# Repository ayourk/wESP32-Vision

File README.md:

# wESP32-Vision
OV2640 Camera module AddOn board for wESP32

## Description
This is my reinterpretation of [@xorbit](https://github.com/xorbit)'s Camera module prototype.  Sample Arduino project included.

### PCB Layout
")

### See Also
[xorbit's Projects](https://github.com/xorbit?tab=repositories)

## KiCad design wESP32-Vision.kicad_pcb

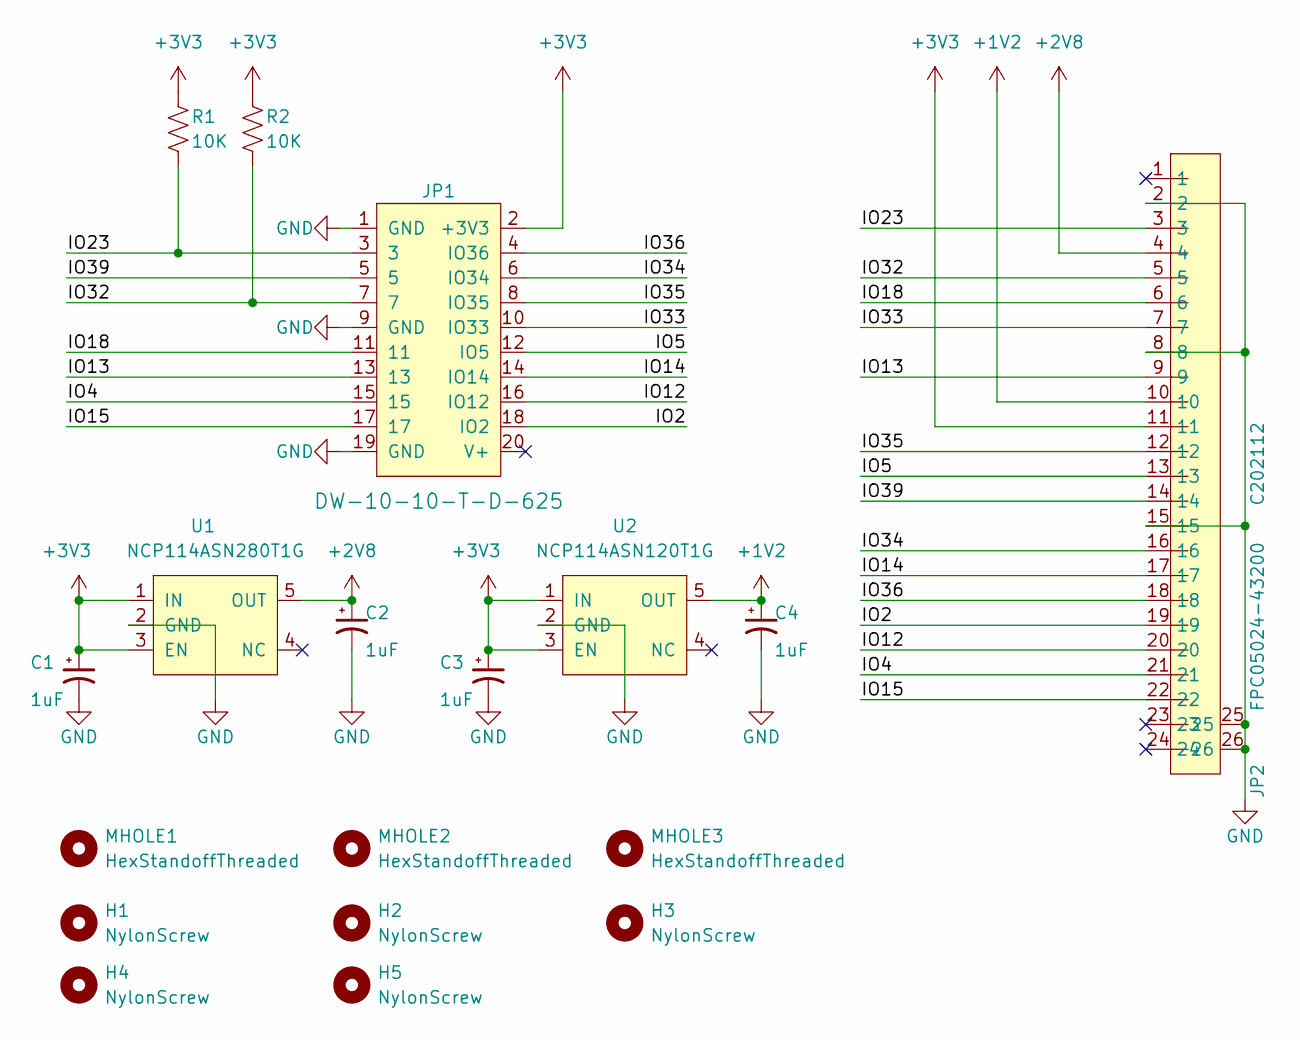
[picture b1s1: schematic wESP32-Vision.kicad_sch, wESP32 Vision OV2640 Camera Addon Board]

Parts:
C1, C2, C3, C4: 1uF; C_0603_1608Metric; MPN CL10A105KB8NNNC; Digi-Key_PN 1276-1860-1-ND
H1, H2, H3, H4, H5: NylonScrew; Screw; MPN 010440WF025; Digi-Key_PN RPC7726-ND
JP1: DW-10-10-T-D-625; SAMTEC_DW-10-XX-X-D-XXX; MPN DW-10-10-T-D-625; LCSC C62032
JP2: FPC05024-43200; FPC-SMD_FH12-24S-0.5SH-55; MPN FH12-24S-0.5SH(55); Digi-Key_PN HFJ124CT-ND
MHOLE1, MHOLE2, MHOLE3: HexStandoffThreaded; MountingHole_3mm; MPN 1902F; Digi-Key_PN 36-1902F-ND
R1, R2: 10K; R_0603_1608Metric; MPN ERJ-UP3F1002V; Digi-Key_PN 10-ERJ-UP3F1002VCT-ND
U1: NCP114ASN280T1G; TSOP-5_L3.0-W1.5-P0.95-LS2.8-BL; MPN NCP114ASN280T1G; LCSC C504890
U2: NCP114ASN120T1G; TSOP-5_L3.0-W1.5-P0.95-LS2.8-BL; MPN NCP114ASN120T1G; LCSC C512862

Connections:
+1V2: C4.1, JP2.10, U2.5 (OUT)
+2V8: C2.1, JP2.4, U1.5 (OUT)
+3V3: C1.1, C3.1, JP1.2 (+3V3), JP2.11, R1.1, R2.1, U1.1 (IN), U1.3 (EN), U2.1 (IN), U2.3 (EN)
/IO2: JP1.18 (IO2), JP2.19
/IO4: JP1.15, JP2.21
/IO5: JP1.12 (IO5), JP2.13
/IO12: JP1.16 (IO12), JP2.20
/IO13: JP1.13, JP2.9
/IO14: JP1.14 (IO14), JP2.17
/IO15: JP1.17, JP2.22
/IO18: JP1.11, JP2.6
/IO23: JP1.3, JP2.3, R1.2
/IO32: JP1.7, JP2.5, R2.2
/IO33: JP1.10 (IO33), JP2.7
/IO34: JP1.6 (IO34), JP2.16
/IO35: JP1.8 (IO35), JP2.12
/IO36: JP1.4 (IO36), JP2.18
/IO39: JP1.5, JP2.14
GND: C1.2, C2.2, C3.2, C4.2, JP1.1 (GND), JP1.9 (GND), JP1.19 (GND), JP2.2, JP2.8, JP2.15, JP2.25, JP2.26, U1.2 (GND), U2.2 (GND)

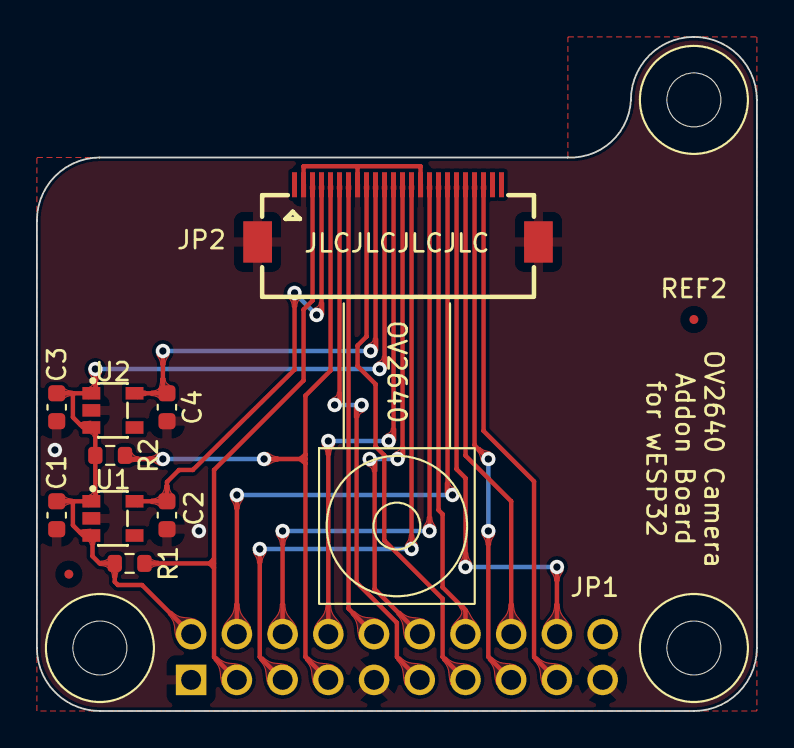
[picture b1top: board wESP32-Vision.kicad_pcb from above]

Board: 2 copper layers, 40.0 x 37.5 mm, 21 parts (1 on the bottom side), 19 nets.

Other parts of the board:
GRAPHIC: OV2640
REF1, REF2: Fiducial_0.5mm_Mask1.5mm

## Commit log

2024-04-09 Initial commit of KiCAD 6.x files and related Arduino Project.
